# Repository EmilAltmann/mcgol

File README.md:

# MCGoL

MCGoL ist ein modulares Open-Source-Platinendesign für **Conway's Game of Life**, das als kollaborative Aufgabe in einzelnen Modulen aufgebaut und zusammengesetzt werden kann.

## Was ist Conway's Game of Life?

Conway's Game of Life ist ein zellulärer Automat auf einem Raster aus Zellen. Jede Zelle ist entweder „lebendig“ oder „tot“. In jedem Schritt wird der nächste Zustand ausschließlich aus den Nachbarzellen berechnet – dadurch entstehen aus einfachen Regeln komplexe, oft überraschende Muster.

## Technischer Ansatz von MCGoL

Die Matrix ist **ausschließlich aus diskreten Logikbausteinen** aufgebaut.
Dazu gehören unter anderem:

- 4-Bit-Addierer
- Schmitt-Trigger
- Triple-AND-Gatter
- Flip-Flops

In der Matrix selbst werden **keine Mikrocontroller** eingesetzt.

## Anleitung

➡️ **[Anleitung öffnen (PDF)](./docs/Anleitung.pdf)**

➡️ **[Videoanleitung](https://youtu.be/6fUdp8ToV98?si=Gxxmejqb-pIHadAP)**

## Interaktive BOM-/Board-Ansicht

Die interaktive Ansicht ist hier im Repository enthalten:

- [iBOM öffnen](https://emilaltmann.github.io/mcgol/ibom.html)

## Projektstruktur

- `README.md` – Projekt-Startseite
- `plakat.png` – Bannerbild
- `ibom.html` – interaktive BOM-/Board-Ansicht
- `docs/Anleitung.pdf` – Projektanleitung
- `hardware/pcb/` – KiCad-Projektdateien (Schaltplan, PCB, Projektdatei)
- `hardware/cad/` – CAD-/3D-Artefakte

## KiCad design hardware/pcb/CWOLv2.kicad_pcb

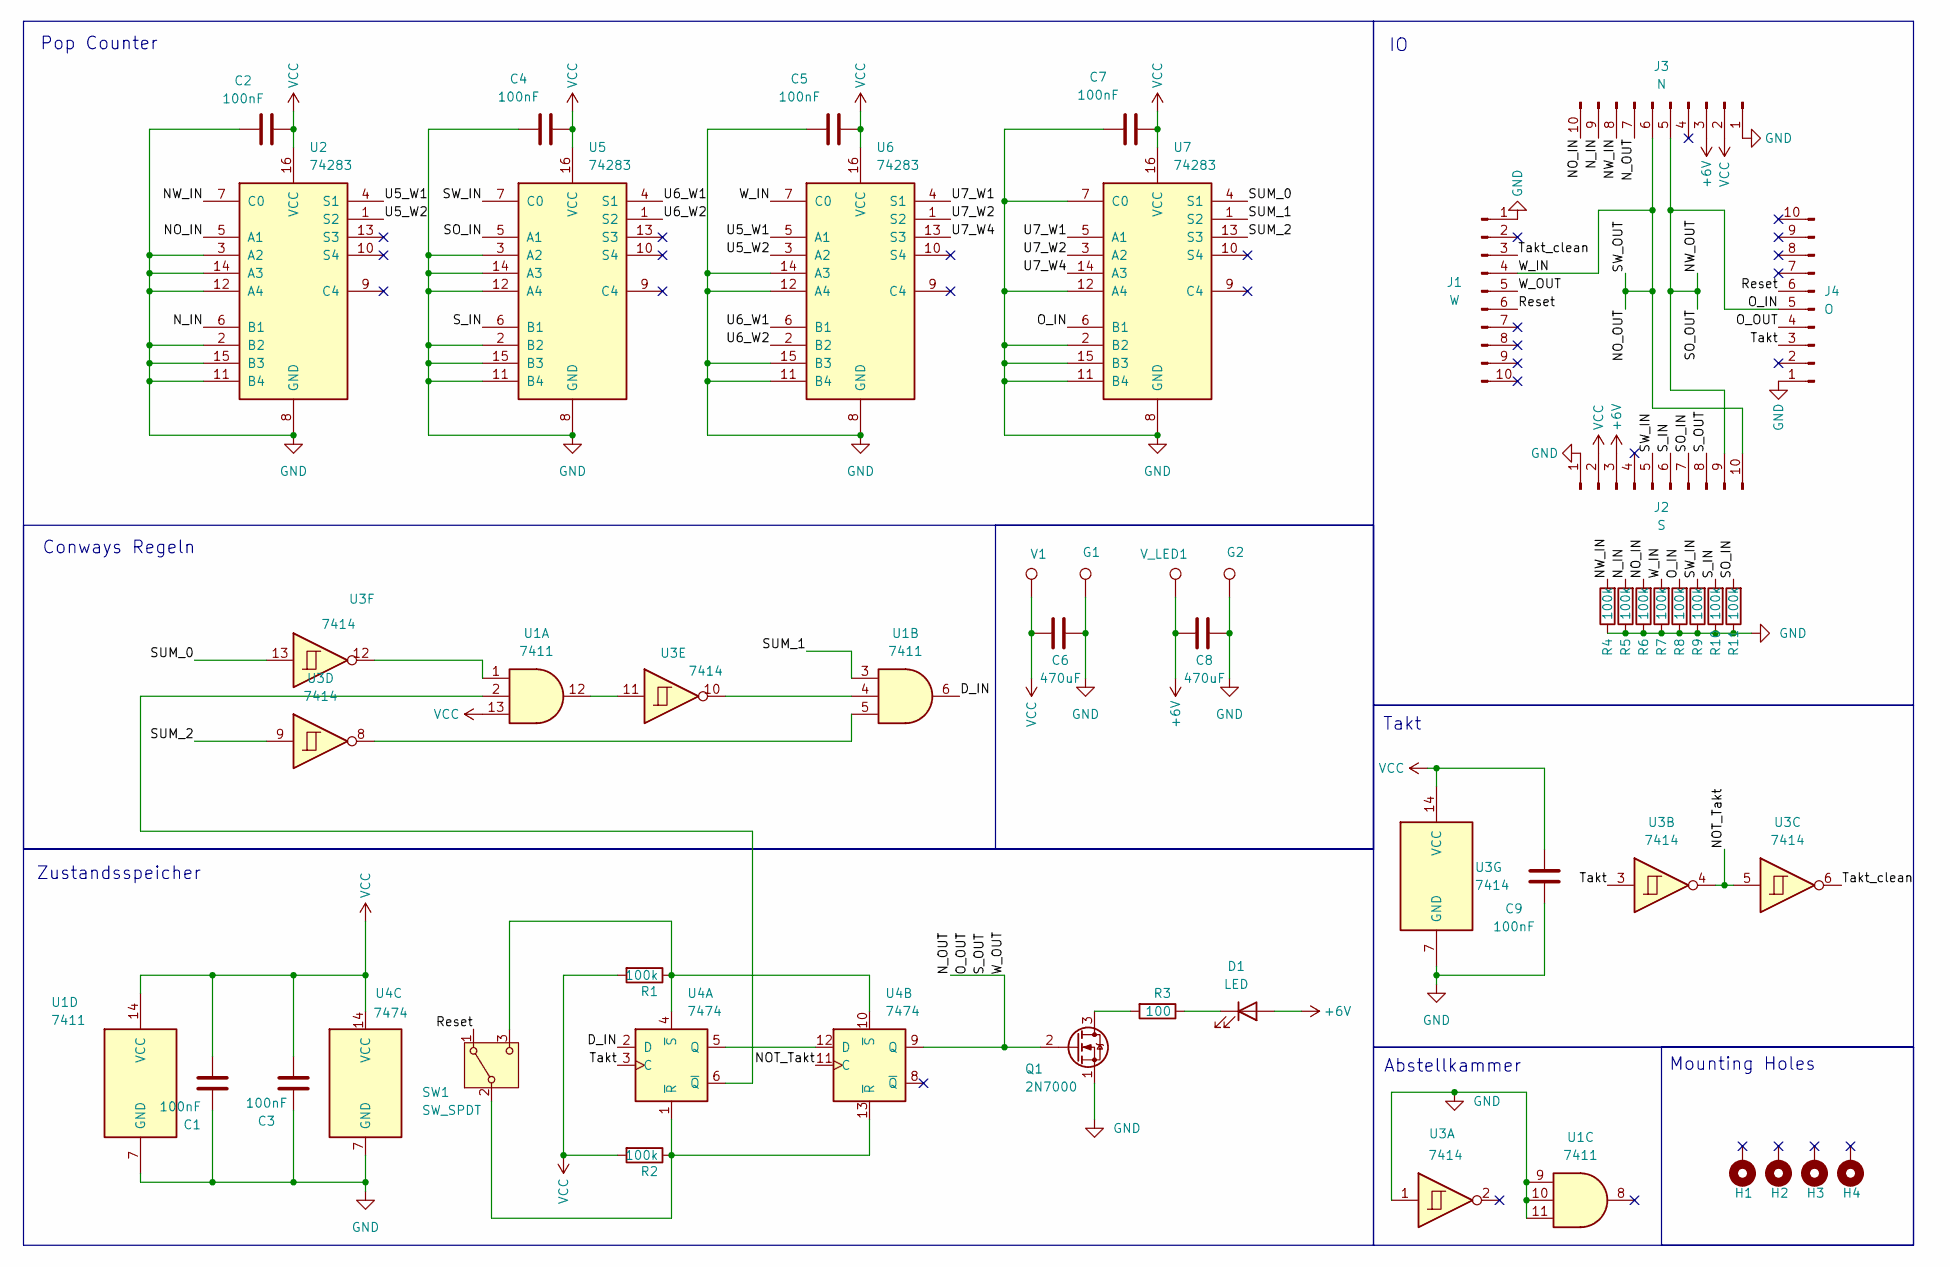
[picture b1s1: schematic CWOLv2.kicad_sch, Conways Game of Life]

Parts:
C1, C2, C3, C4, C5, C7, C9: 100nF; C_Disc_D5.0mm_W2.5mm_P2.50mm_3PIN
C6, C8: 470uF; CP_Radial_D5.0mm_P2.50mm
D1: LED; LED_D20.0mm
G1, G2: TestPoint; TestPoint_THTPad_D3.0mm_Drill1.5mm
H1, H2, H3, H4: MountingHole_Pad; MountingHole_3.2mm_M3_Pad_Via
J1: W; PinHeader_1x10_P2.54mm_Horizontal
J2: S; PinHeader_1x10_P2.54mm_Horizontal
J3: N; PinSocket_1x10_P2.54mm_Horizontal
J4: O; PinSocket_1x10_P2.54mm_Horizontal
Q1: 2N7000; TO-92_Inline_Wide
R1, R2, R4, R5, R6, R7, R8, R9, R10, R11: 100k; R_Axial_DIN0207_L6.3mm_D2.5mm_P10.16mm_Horizontal_Fett3
R3: 100; R_Axial_DIN0207_L6.3mm_D2.5mm_P10.16mm_Horizontal_Fett2
SW1: SW_SPDT; SW_Slide-03_Wuerth-WS-SLTV_10x2.5x6.4_P2.54mm
U1: 7411; DIP-14_W7.62mm_Socket_LongPads
U2, U5, U6, U7: 74283; DIP-16_W7.62mm_Socket_LongPads
U3: 7414; DIP-14_W7.62mm_Socket_LongPads
U4: 7474; DIP-14_W7.62mm_Socket_LongPads
V1: TestPoint; TestPoint_THTPad_D3.0mm_Drill1.5mm
V_LED1: TestPoint; TestPoint_THTPad_D3.0mm_Drill1.5mm

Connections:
+6V: C8.1, D1.2 (A), J2.3, J3.3, V_LED1.1 (1_1)
/D_IN: U1.6, U4.2 (D)
/NOT_Takt: U3.4, U3.5, U4.11 (C)
/NO_IN: J3.10, R6.2, U2.5 (A1)
/NO_OUT: J1.4, J2.10, J3.6, R7.2, U6.7 (C0)
/NW_IN: J3.8, R4.2, U2.7 (C0)
/NW_OUT: J2.9, J3.5, J4.5, R8.2, U7.6 (B1)
/N_IN: J3.9, R5.2, U2.6 (B1)
/N_OUT: J1.5, J2.8, J3.7, J4.4, Q1.2 (G), U4.9 (Q)
/Reset: J1.6, J4.6, SW1.1 (A)
/SO_IN: J2.7, R11.2, U5.5 (A1)
/SUM_0: U3.13, U7.4 (S1)
/SUM_1: U1.3, U7.1 (S2)
/SUM_2: U3.9, U7.13 (S3)
/SW_IN: J2.5, R9.2, U5.7 (C0)
/S_IN: J2.6, R10.2, U5.6 (B1)
/Takt: J4.3, U3.3, U4.3 (C)
/Takt_clean: J1.3, U3.6
/U5_W1: U2.4 (S1), U6.5 (A1)
/U5_W2: U2.1 (S2), U6.3 (A2)
/U6_W1: U5.4 (S1), U6.6 (B1)
/U6_W2: U5.1 (S2), U6.2 (B2)
/U7_W1: U6.4 (S1), U7.5 (A1)
/U7_W2: U6.1 (S2), U7.3 (A2)
/U7_W4: U6.13 (S3), U7.14 (A3)
GND: C1.1, C2.1, C3.1, C4.1, C5.1, C6.2, C7.1, C8.2, C9.1, G1.1 (1_1), G2.1 (1_1), J1.1, J2.1, J3.1, J4.1, Q1.1 (S), R4.1, R5.1, R6.1, R7.1, R8.1, R9.1, R10.1, R11.1, U1.7 (GND), U1.9, U1.10, U1.11, U2.2 (B2), U2.3 (A2), U2.8 (GND), U2.11 (B4), U2.12 (A4), U2.14 (A3), U2.15 (B3), U3.1, U3.7 (GND), U4.7 (GND), U5.2 (B2), U5.3 (A2), U5.8 (GND), U5.11 (B4), U5.12 (A4), U5.14 (A3), U5.15 (B3), U6.8 (GND), U6.11 (B4), U6.12 (A4), U6.14 (A3), U6.15 (B3), U7.2 (B2), U7.7 (C0), U7.8 (GND), U7.11 (B4), U7.12 (A4), U7.15 (B3)
unnamed: D1.1 (K), R3.1
unnamed: Q1.3 (D), R3.2
unnamed: R2.1, SW1.2 (B), U4.1 (~R), U4.13 (~R)
unnamed: R1.1, SW1.3 (C), U4.4 (~S), U4.10 (~S)
unnamed: U1.1, U3.12
unnamed: U1.4, U3.10
unnamed: U1.5, U3.8
unnamed: U1.12, U3.11
unnamed: U4.5 (Q), U4.12 (D)
unnamed: U1.2, U4.6 (~Q)
VCC: C1.2, C2.2, C3.2, C4.2, C5.2, C6.1, C7.2, C9.2, J2.2, J3.2, R1.2, R2.2, U1.13, U1.14 (VCC), U2.16 (VCC), U3.14 (VCC), U4.14 (VCC), U5.16 (VCC), U6.16 (VCC), U7.16 (VCC), V1.1 (1_1)

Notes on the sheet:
Pop Counter
Zustandsspeicher
Conways Regeln
Abstellkammer
Takt
Mounting Holes

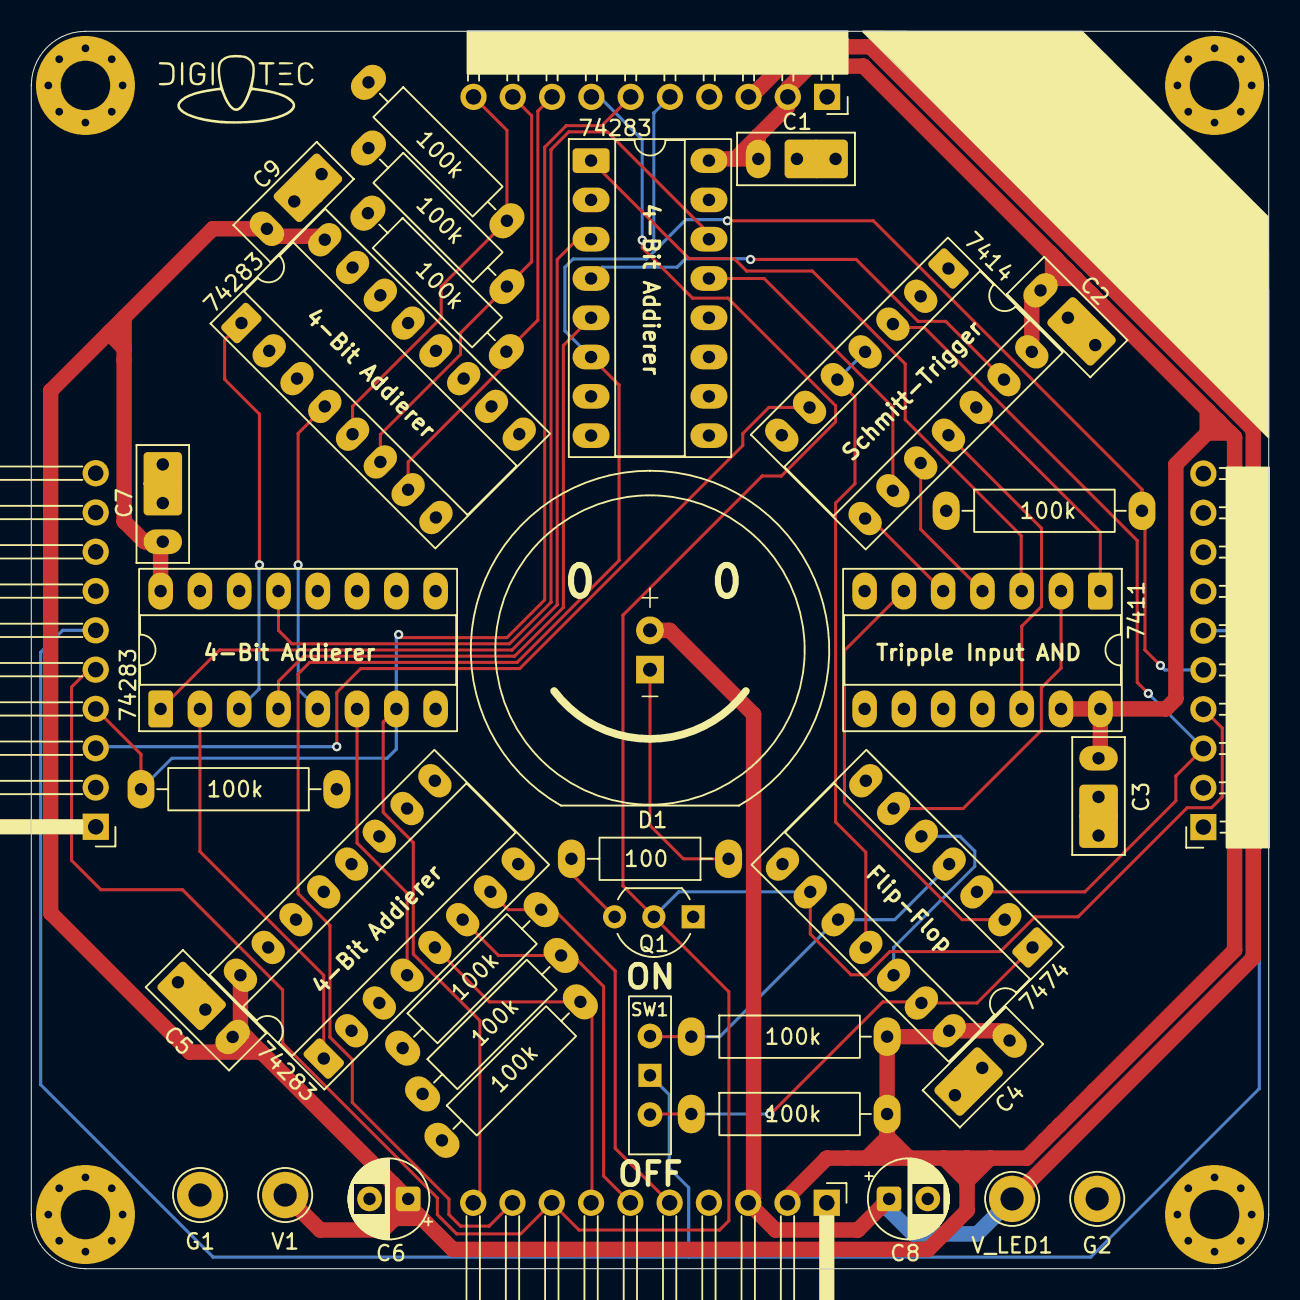
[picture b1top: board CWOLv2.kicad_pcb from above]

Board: 2 copper layers, 80.0 x 80.0 mm, 42 parts (0 on the bottom side), 37 nets.
